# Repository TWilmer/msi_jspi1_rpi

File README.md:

# JSPI1 MSI  to RPI converter

This project builds a JSPI Flash adapter
which allows to recver MSI Flash PIOS with RPi

It features a 1.8V or 3.3V interface. A level
converter is used to translate between
the voltages.

For the RPI the SPI0 is used:

GPIO10, Pin 19, MOSI
GPIO9, Pin 21, MISO
GPIO11, Pin 23, SCLK
GPIO8, Pin 24, CS

The two addition Pin of the 2x6 Connector are driven statically. But because these pins are going to be ran through the level converter it's a nice feature to have a UART Adapter for 1.8V Boards.

GPIO14, Pin 8, TX
GPIO15, Pin 10, RX

# High level Design

The connectors are done through severa jumper, so that one can swap the pin setting.
The board contains a break out are so that the adapter from 2.0 mm spacing to 2.5mm spacing can be broken off.

The voltage Regulator is AMS1117-1.8
The Level shifter is TXS0108EPWR  SOP-20

The Target is connected to Port A
The RPI is  connected to Port B
where VCC-A has to be smaller than VCC-B

The OE has to be driven from VCC-A thus we keep it always high.

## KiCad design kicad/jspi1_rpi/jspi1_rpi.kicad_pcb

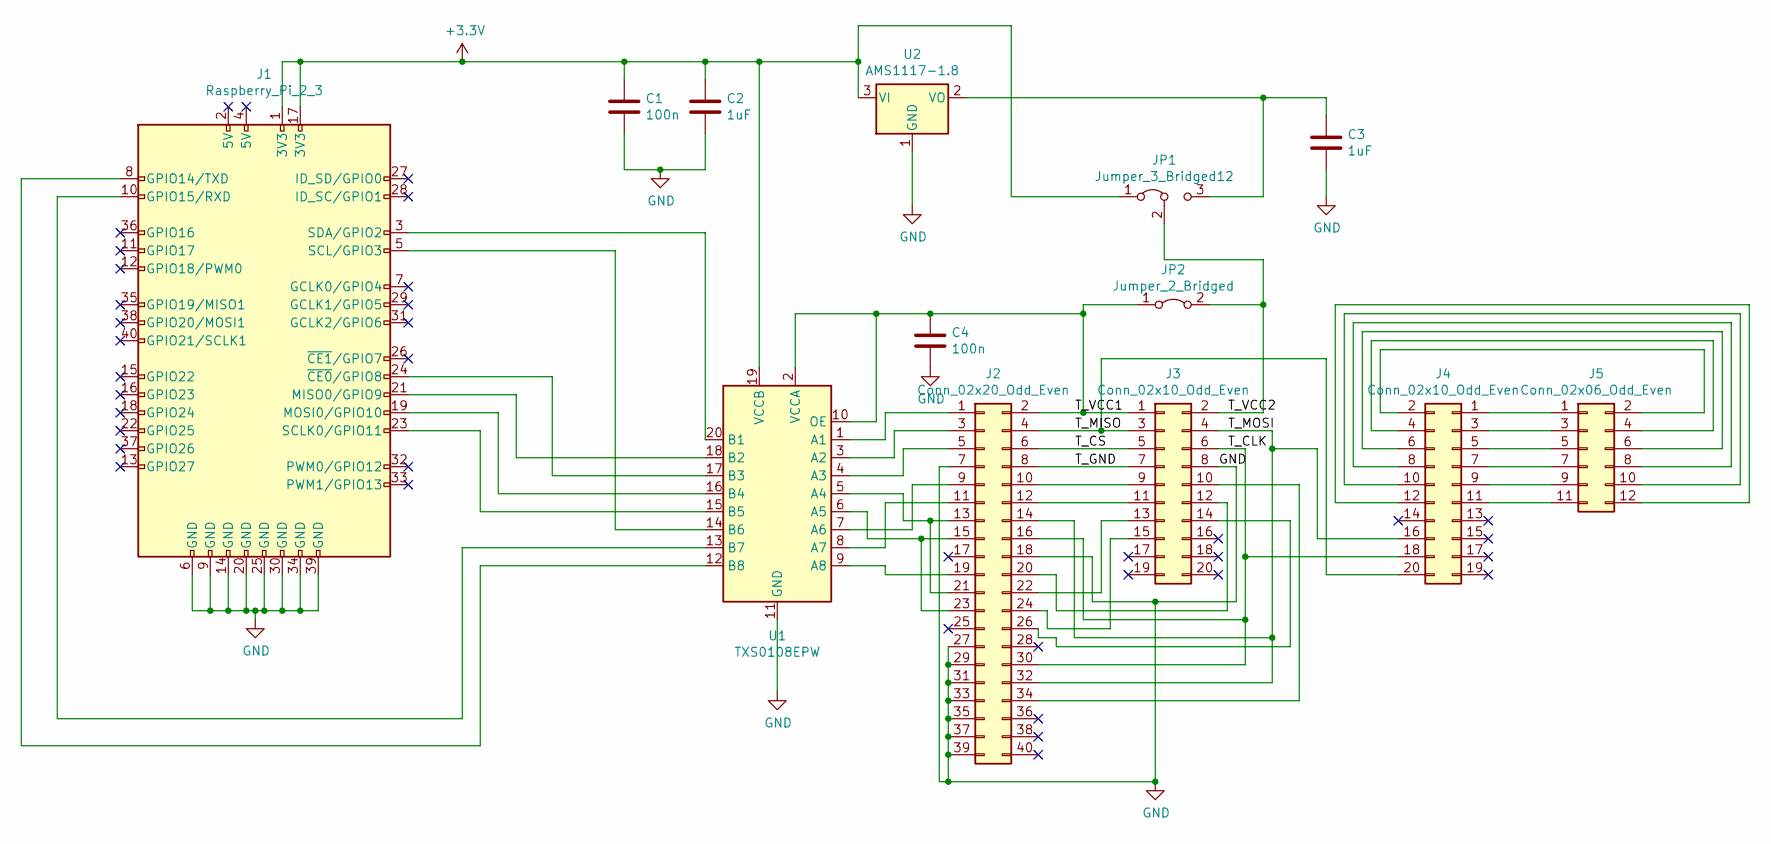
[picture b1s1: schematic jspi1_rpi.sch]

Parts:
C1, C4: 100n; C_0805_2012Metric_Pad1.18x1.45mm_HandSolder
C2, C3: 1uF; C_0805_2012Metric_Pad1.18x1.45mm_HandSolder
J1: Raspberry_Pi_2_3; PinSocket_2x20_P2.54mm_Vertical
J2: Conn_02x20_Odd_Even; PinHeader_2x20_P2.54mm_Vertical
J3, J4: Conn_02x10_Odd_Even; IDC-Header_2x10_P2.54mm_Vertical
J5: Conn_02x06_Odd_Even; PinSocket_2x06_P2.00mm_Vertical
JP1: Jumper_3_Bridged12; PinHeader_1x03_P2.54mm_Vertical
JP2: Jumper_2_Bridged; PinHeader_1x02_P2.54mm_Vertical
U1: TXS0108EPW; TSSOP-20_4.4x6.5mm_P0.65mm
U2: AMS1117-1.8; SOT-223-3_TabPin2

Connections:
+3V3: C1.1, C2.1, J1.1 (3V3), J1.17 (3V3), JP1.1 (A), U1.19 (VCCB), U2.3 (VI)
/T_CLK: J2.16, J2.30, J3.6, J4.18
/T_CS: J2.6, J3.5
/T_GND: J2.8, J3.7
/T_MISO: J2.4, J3.3, J4.20
/T_MOSI: J2.14, J2.32, J3.4, J4.16
/T_VCC1: C4.1, J2.2, J3.1, JP2.1 (A), U1.2 (VCCA), U1.10 (OE)
/T_VCC2: J3.2, JP1.2 (C), JP2.2 (B)
GND: C1.2, C2.2, C3.2, C4.2, J1.6 (GND), J1.9 (GND), J1.14 (GND), J1.20 (GND), J1.25 (GND), J1.30 (GND), J1.34 (GND), J1.39 (GND), J2.7, J2.18, J2.27, J2.29, J2.31, J2.33, J2.35, J2.37, J2.39, J3.8, U1.11 (GND), U2.1 (GND)
unnamed: C3.1, JP1.3 (B), U2.2 (VO)
unnamed: J1.3 (SDA/GPIO2), U1.20 (B1)
unnamed: J1.5 (SCL/GPIO3), U1.14 (B6)
unnamed: J1.8 (GPIO14/TXD), U1.12 (B8)
unnamed: J1.10 (GPIO15/RXD), U1.13 (B7)
unnamed: J1.19 (MOSI0/GPIO10), U1.16 (B4)
unnamed: J1.21 (MISO0/GPIO9), U1.18 (B2)
unnamed: J1.23 (SCLK0/GPIO11), U1.15 (B5)
unnamed: J1.24 (~CE0~/GPIO8), U1.17 (B3)
unnamed: J2.1, U1.1 (A1)
unnamed: J2.3, U1.3 (A2)
unnamed: J2.5, U1.4 (A3)
unnamed: J2.9, U1.7 (A6)
unnamed: J2.10, J3.9
unnamed: J2.11, U1.8 (A7)
unnamed: J2.12, J3.11
unnamed: J2.13, J2.21, U1.5 (A4)
unnamed: J2.15, J2.23, U1.6 (A5)
unnamed: J2.19, U1.9 (A8)
unnamed: J2.20, J3.12
unnamed: J2.22, J3.13
unnamed: J2.24, J3.15
unnamed: J2.26, J3.14
unnamed: J2.34, J3.10
unnamed: J4.1, J5.1
unnamed: J4.2, J5.2
unnamed: J4.3, J5.3
unnamed: J4.4, J5.4
unnamed: J4.5, J5.5
unnamed: J4.6, J5.6
unnamed: J4.7, J5.7
unnamed: J4.8, J5.8
unnamed: J4.9, J5.9
unnamed: J4.10, J5.10
unnamed: J4.11, J5.11
unnamed: J4.12, J5.12

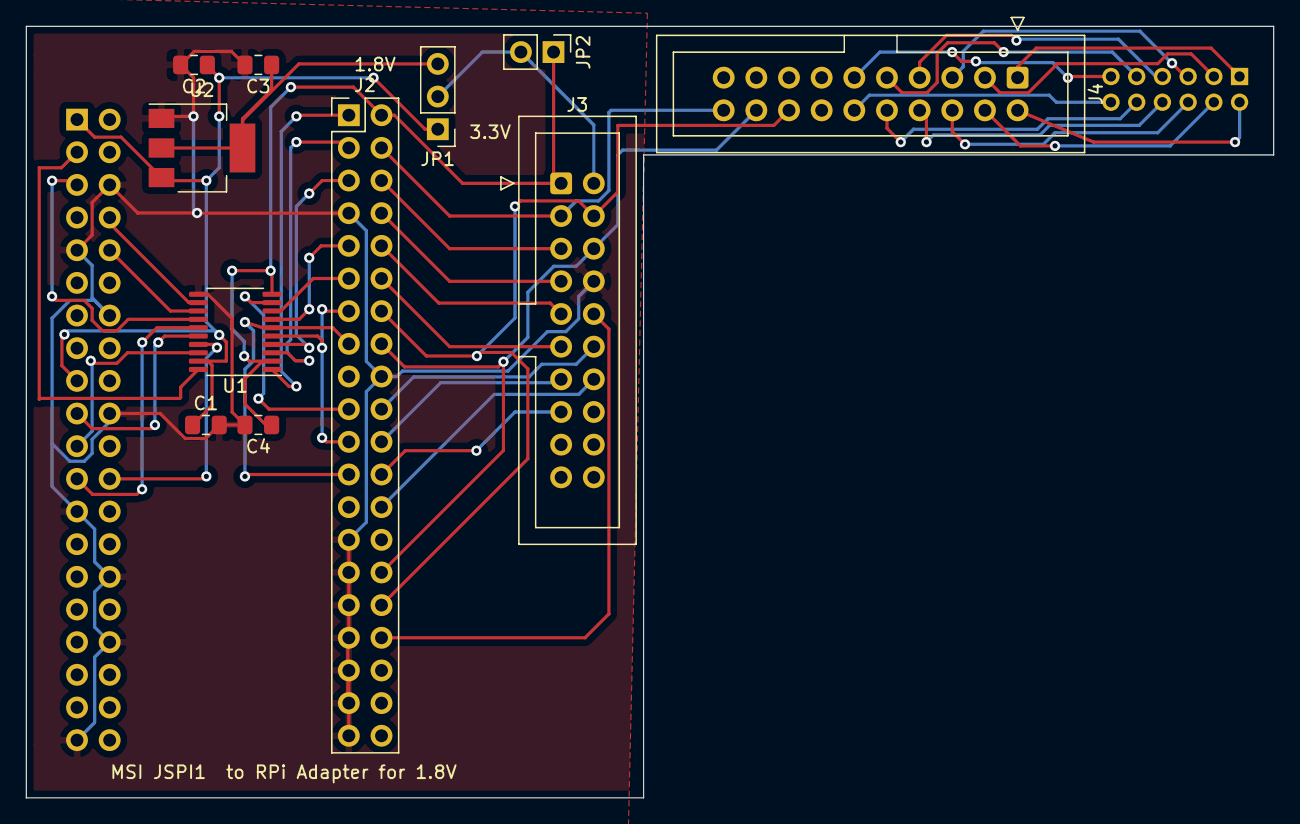
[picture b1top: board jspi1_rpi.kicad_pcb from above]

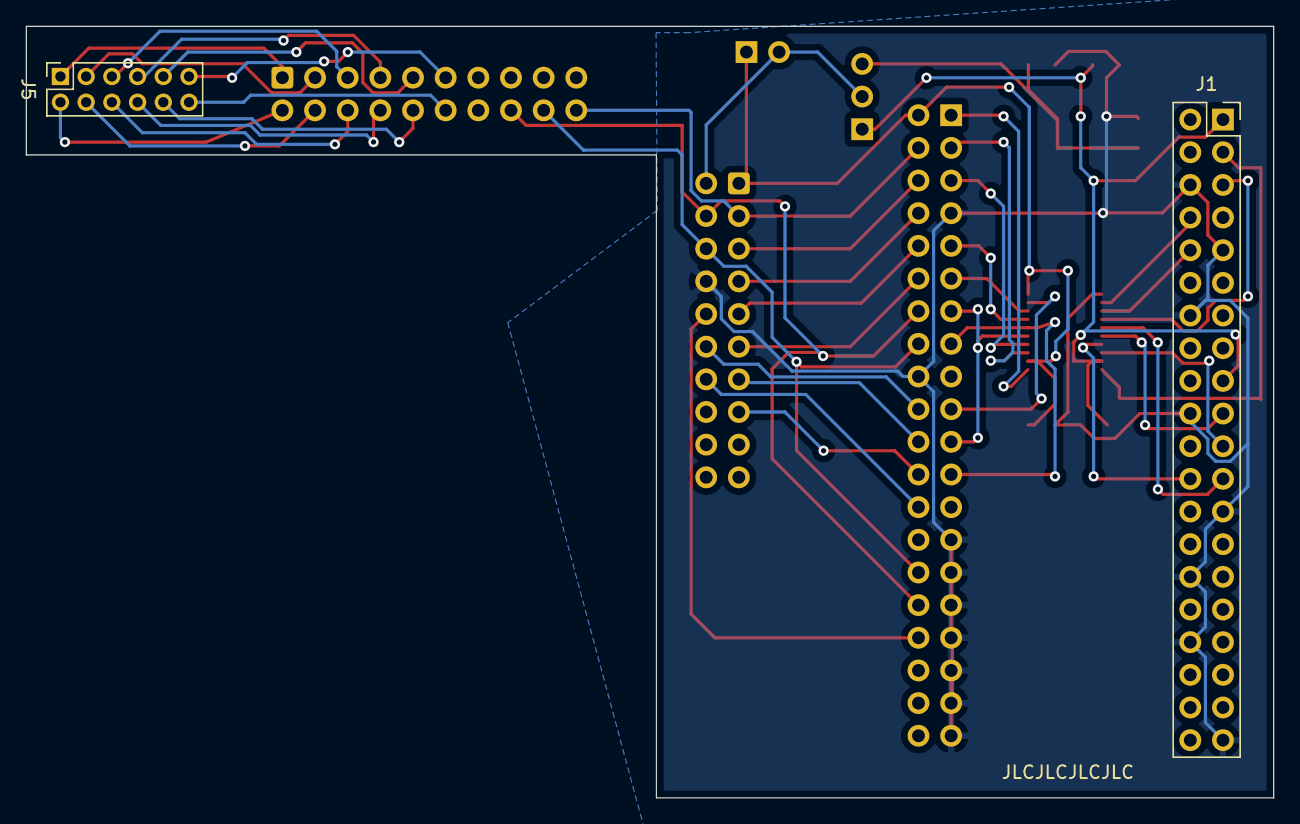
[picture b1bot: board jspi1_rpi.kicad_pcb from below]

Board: 2 copper layers, 97.0 x 60.0 mm, 13 parts (2 on the bottom side), 45 nets.

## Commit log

2022-02-05 Inital commit with pinout and goal
2022-02-05 First cirquit
2022-02-05 First PCB
2022-02-05 routed pcb
2022-02-06 Order v1
